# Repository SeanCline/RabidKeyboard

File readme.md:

# RabidKeyboard

This project is an ode to the old-school Cooler Master [QuickFire Rapid](https://deskthority.net/wiki/Cooler_Master_QuickFire_Rapid) TKL keyboard -- a board that introduced many people to the mechanical keyboard hobby years ago.

Over time, upgrade parts for these old mechanical keyboards have become hard to find. This project attempts to solve that by providing PCB designs that can be manufactured by services like [JLCPCB](https://jlcpcb.com/) or [PCBWay](https://www.pcbway.com/).

With the PCBs in this repository, you could:
 - Build a TKL keyboard from scratch.
 - Replace the mini-USB plug with USB-C on your Cooler Master QFR.
 - Replace the PCB in your QFR (or compatible) with a custom design running the [KMK firmware](https://github.com/KMKfw/kmk_firmware).
 - Replace the plate in your TKL keyboard with one made of FR-4 and support for more stabilizers. (Stock Costar, Cherry Plate mount, or PCB mount when the PCB is also replaced.)

## PCB
The PCB is designed in [KiCad](https://www.kicad.org/) to be easily soldered by hand. At its heart is the [RP2040 Stamp](https://www.lectronz.com/products/rp2040-stamp), which fits nicely beside the arrow keys.

## Plate
The plate is just a PCB without any copper traces. When sending it for manufacture, you can select the thickness of FR-4 to get the level of flex you like.

It's generated by copying the User.1 layer out of the PCB design and changing the layer to Edge.Cuts. The keyswitch footprints use the User.1 layer for the plate cutout which makes sure the plate cutouts always line up with the key switch location on the PCB.

> Note: This abuses the routing capabilities of a PCB manufacturer, so they'll likely charge extra for their trouble.

## Costar USB-C Daughterboard
This PCB replaces the original mini-USB daughterboard in the Cooler Master QFR. Mounting holes match the [original PCB](reference/Quickfire%20Rapid/USB%20Daughterboard%20-%20Front.jpg) so it's a drop-in replacement. A little bit of filing is required to widen the mini-USB hole the width of the USB-C port.

## YMDK USB-C Daughterboard
Just like the Cooler Master QFR, Filco Majestouch 2, and KBParadise V80, the RabidKeyboard PCB in this repo fits into the YMDK F87 aluminum case.
[[Amazon]](https://amzn.com/dp/B06XNTWXWL)
[[AliExpress]](https://www.aliexpress.us/item/2251832431251957.html)
[[Ymdkey]](https://ymdkey.com/products/f87-tkl-cnc-anodized-aluminum-case-for-filco-cm-cooler-master-87-tenkeyless)

Unfortunately, the USB daughterboard that [comes with](reference/YMDK/YMDK%20Usb%20-%20Back.png) the YMDK F87 case lacks the [required 5.1k resistors](https://hackaday.com/2023/01/04/all-about-usb-c-resistors-and-emarkers/). It works fine when plugged in using a USB-C to Type-A cable, but does not function when plugged in using a USB-C to USB-C cable. It also lacks protection circuitry. The design in this repository is a drop in replacement with some improvements:
 - 5.1k CC1 and CC2 sense resistors to work with USB-C cables.
 - [TVS diodes](https://en.wikipedia.org/wiki/Surge_protector#Transient_voltage_suppressor) to keep static shocks from reaching the microcontroller.
 - 500mA polyfuse to protect from short circuits.
 - Reverse polarity protection diode.
 - Ferrite beads to reduce high frequency EMI.

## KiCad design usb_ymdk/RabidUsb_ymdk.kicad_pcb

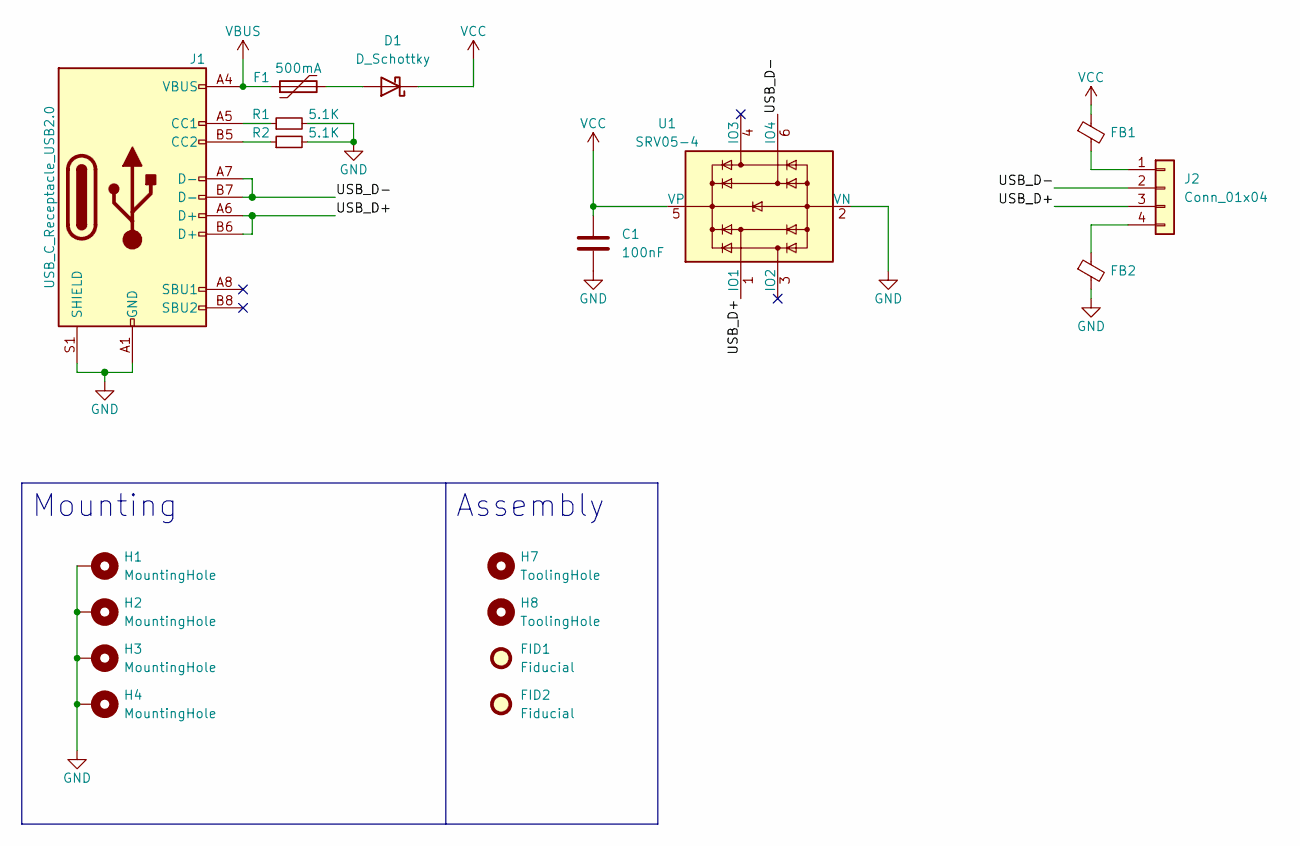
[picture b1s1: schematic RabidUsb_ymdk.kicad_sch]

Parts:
C1: 100nF; C_0603_1608Metric; LCSC C14663
D1: D_Schottky; D_SOD-123; LCSC C8598
F1: 500mA; Fuse_1812_4532Metric; LCSC C12559
FB1, FB2: FerriteBead_Small; L_0805_2012Metric; LCSC C67451
FID1, FID2: Fiducial; Fiducial_1mm_Mask2mm
H1, H2, H3, H4: MountingHole; MountingHole_.12in_Pad_.02in
H7, H8: ToolingHole; ToolingHole_1.152mm
J1: USB_C_Receptacle_USB2.0; USB_C_Receptacle_XKB_U262-16XN-4BVC11; LCSC C319148
J2: Conn_01x04; PinHeader_1x04_P2.00mm_Fingers
R1, R2: 5.1K; R_0603_1608Metric; LCSC C23186
U1: SRV05-4; SOT-23-6; LCSC C85364

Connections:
/USB_D+: J1.A6 (D+), J1.B6 (D+), J2.3, U1.1 (IO1)
/USB_D-: J1.A7 (D-), J1.B7 (D-), J2.2, U1.6 (IO4)
GND: C1.2, FB2.2, H1.1, H2.1, H3.1, H4.1, J1.A1 (GND), J1.A12 (GND), J1.B1 (GND), J1.B12 (GND), J1.S1 (SHIELD), R1.2, R2.2, U1.2 (VN)
unnamed: D1.2 (A), F1.2
unnamed: FB1.2, J2.1
unnamed: FB2.1, J2.4
unnamed: J1.A5 (CC1), R1.1
unnamed: J1.B5 (CC2), R2.1
VBUS: F1.1, J1.A4 (VBUS), J1.A9 (VBUS), J1.B4 (VBUS), J1.B9 (VBUS)
VCC: C1.1, D1.1 (K), FB1.1, U1.5 (VP)

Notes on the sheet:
Assembly
Mounting

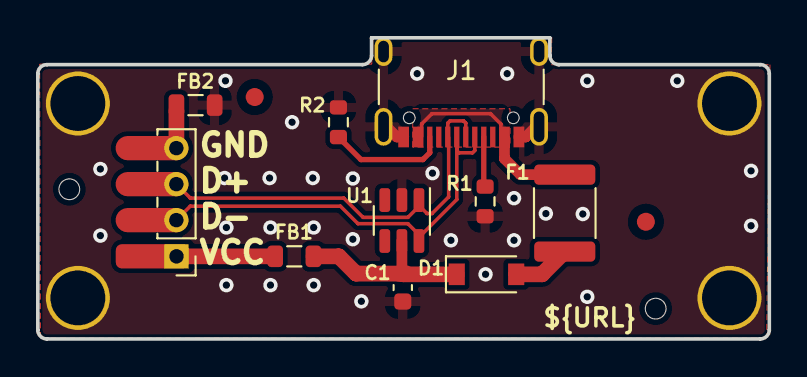
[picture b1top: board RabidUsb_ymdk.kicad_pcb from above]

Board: 2 copper layers, 40.6 x 16.7 mm, 18 parts (0 on the bottom side), 10 nets.

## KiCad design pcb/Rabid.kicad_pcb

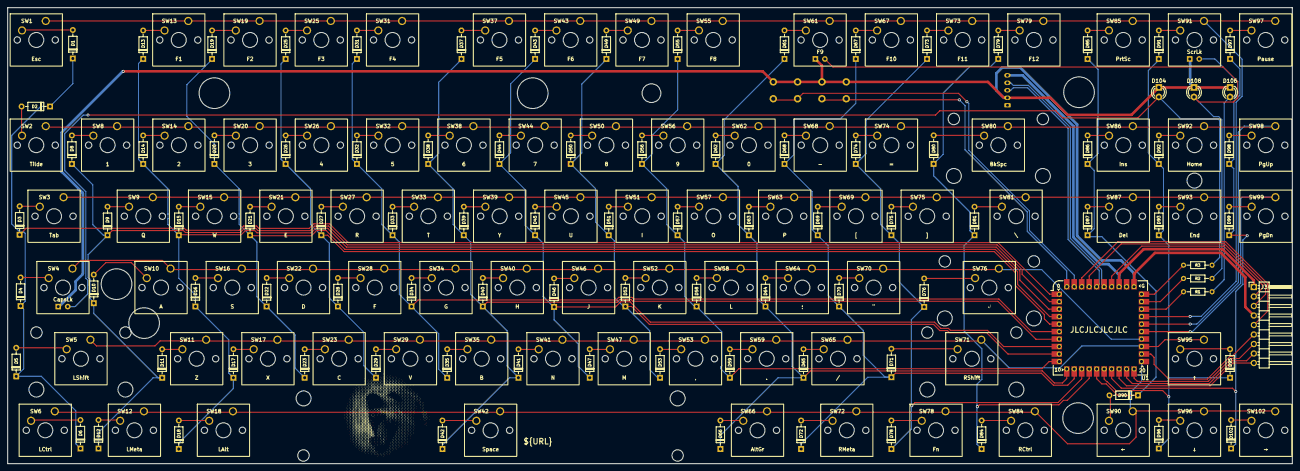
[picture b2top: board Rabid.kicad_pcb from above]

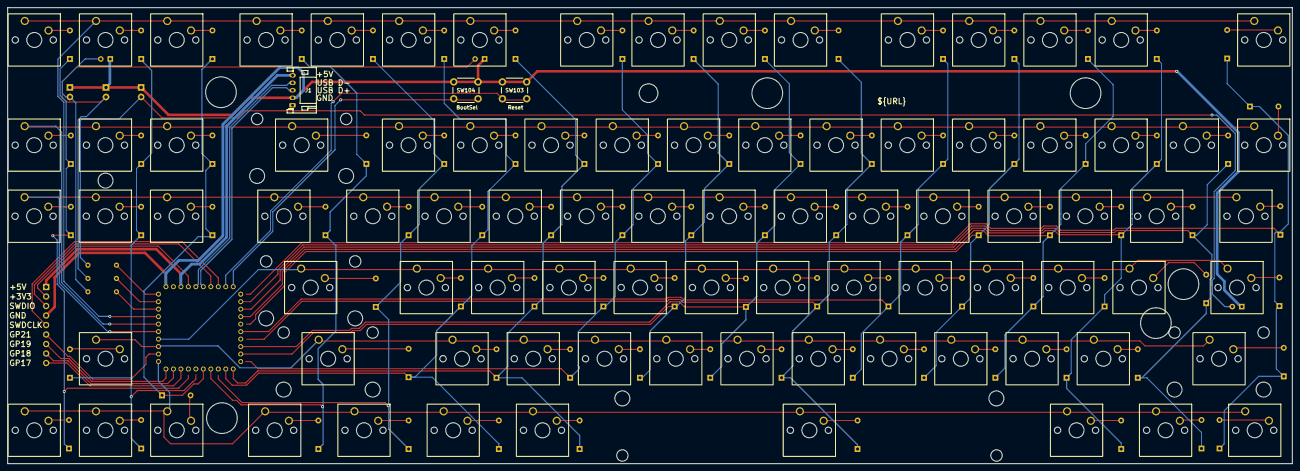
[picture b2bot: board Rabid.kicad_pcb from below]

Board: 2 copper layers, 343.4 x 121.9 mm, 194 parts (3 on the bottom side), 129 nets.

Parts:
D1, D2, D3, D4, D5, D6, D8, D9, D10, D11, D12, D13, D14, D15, D16, D17, D18, D19, D20, D21, D22, D23, D25, D26, D27, D28, D29, D31, D32, D33, D34, D35, D37, D38, D39, D40, D41, D42, D43, D44, D45, D46, D47, D49, D50, D51, D52, D53, D55, D56, D57, D58, D59, D61, D62, D63, D64, D65, D66, D67, D68, D69, D70, D71, D72, D73, D74, D75, D76, D78, D79, D80, D81, D84, D85, D86, D87, D90, D91, D92, D93, D95, D96, D97, D98, D99, D102: 1N4148; D_DO-35_SOD27_P7.62mm_Horizontal
D104: CapsLock; LED_D3.0mm
D106: ScrollLock; LED_D3.0mm
D108: MetaLock; LED_D3.0mm
G1: LOGO; RabidKeyboardLogo
H1, H2, H4, H5, H6, H7: MountingHole_8.2mm
H3: MountingHole_5mm
H8: MountingHole_4mm
J1: USB Connector; JST_PH_S5B-PH-K_1x05_P2.00mm_Horizontal
J3: GPIO Debug Header; PinHeader_1x09_P2.54mm_Horizontal
R1, R2, R3: 560; R_Axial_DIN0204_L3.6mm_D1.6mm_P7.62mm_Horizontal
SW1: Esc; SW_Cherry_MX_1.00u_PCB
SW2: Tilde; SW_Cherry_MX_1.00u_PCB
SW3: Tab; SW_Cherry_MX_1.50u_PCB
SW4: CapsLk; SW_Cherry_MX_1.75u_PCB_LED
SW5: LShift; SW_Cherry_MX_2.25u_PCB
SW6: LCtrl; SW_Cherry_MX_1.25u_PCB
SW8: 1; SW_Cherry_MX_1.00u_PCB
SW9: Q; SW_Cherry_MX_1.00u_PCB
SW10: A; SW_Cherry_MX_1.00u_PCB
SW11: Z; SW_Cherry_MX_1.00u_PCB
SW12: LMeta; SW_Cherry_MX_1.25u_PCB
SW13: F1; SW_Cherry_MX_1.00u_PCB
SW14: 2; SW_Cherry_MX_1.00u_PCB
SW15: W; SW_Cherry_MX_1.00u_PCB
SW16: S; SW_Cherry_MX_1.00u_PCB
SW17: X; SW_Cherry_MX_1.00u_PCB
SW18: LAlt; SW_Cherry_MX_1.25u_PCB
SW19: F2; SW_Cherry_MX_1.00u_PCB
SW20: 3; SW_Cherry_MX_1.00u_PCB
SW21: E; SW_Cherry_MX_1.00u_PCB
SW22: D; SW_Cherry_MX_1.00u_PCB
SW23: C; SW_Cherry_MX_1.00u_PCB
SW25: F3; SW_Cherry_MX_1.00u_PCB
SW26: 4; SW_Cherry_MX_1.00u_PCB
SW27: R; SW_Cherry_MX_1.00u_PCB
SW28: F; SW_Cherry_MX_1.00u_PCB
SW29: V; SW_Cherry_MX_1.00u_PCB
SW31: F4; SW_Cherry_MX_1.00u_PCB
SW32: 5; SW_Cherry_MX_1.00u_PCB
SW33: T; SW_Cherry_MX_1.00u_PCB
SW34: G; SW_Cherry_MX_1.00u_PCB
SW35: B; SW_Cherry_MX_1.00u_PCB
SW37: F5; SW_Cherry_MX_1.00u_PCB
SW38: 6; SW_Cherry_MX_1.00u_PCB
SW39: Y; SW_Cherry_MX_1.00u_PCB
SW40: H; SW_Cherry_MX_1.00u_PCB
SW41: N; SW_Cherry_MX_1.00u_PCB
SW42: Space; SW_Cherry_MX_6.25u_PCB_MirroredStabs
SW43: F6; SW_Cherry_MX_1.00u_PCB
SW44: 7; SW_Cherry_MX_1.00u_PCB
SW45: U; SW_Cherry_MX_1.00u_PCB
SW46: J; SW_Cherry_MX_1.00u_PCB
SW47: M; SW_Cherry_MX_1.00u_PCB
SW49: F7; SW_Cherry_MX_1.00u_PCB
SW50: 8; SW_Cherry_MX_1.00u_PCB
SW51: I; SW_Cherry_MX_1.00u_PCB
SW52: K; SW_Cherry_MX_1.00u_PCB
SW53: ,; SW_Cherry_MX_1.00u_PCB
SW55: F8; SW_Cherry_MX_1.00u_PCB
SW56: 9; SW_Cherry_MX_1.00u_PCB
SW57: O; SW_Cherry_MX_1.00u_PCB
SW58: L; SW_Cherry_MX_1.00u_PCB
SW59: .; SW_Cherry_MX_1.00u_PCB
SW61: F9; SW_Cherry_MX_1.00u_PCB_LED
SW62: 0; SW_Cherry_MX_1.00u_PCB
SW63: P; SW_Cherry_MX_1.00u_PCB
SW64: ;; SW_Cherry_MX_1.00u_PCB
SW65: /; SW_Cherry_MX_1.00u_PCB
SW66: AltGr; SW_Cherry_MX_1.25u_PCB
SW67: F10; SW_Cherry_MX_1.00u_PCB
SW68: -; SW_Cherry_MX_1.00u_PCB
SW69: [; SW_Cherry_MX_1.00u_PCB
SW70: "; SW_Cherry_MX_1.00u_PCB
SW71: RShift; SW_Cherry_MX_2.75u_PCB
SW72: RMeta; SW_Cherry_MX_1.25u_PCB
SW73: F11; SW_Cherry_MX_1.00u_PCB
SW74: =; SW_Cherry_MX_1.00u_PCB
SW75: ]; SW_Cherry_MX_1.00u_PCB
SW76: ↲; SW_Cherry_MX_2.25u_PCB
SW78: Fn; SW_Cherry_MX_1.25u_PCB
SW79: F12; SW_Cherry_MX_1.00u_PCB
SW80: BkSpc; SW_Cherry_MX_2.00u_PCB
SW81: \; SW_Cherry_MX_1.50u_PCB
SW84: RCtrl; SW_Cherry_MX_1.25u_PCB
SW85: PrtSc; SW_Cherry_MX_1.00u_PCB
SW86: Ins; SW_Cherry_MX_1.00u_PCB
SW87: Del; SW_Cherry_MX_1.00u_PCB
SW90: ←; SW_Cherry_MX_1.00u_PCB
SW91: ScrLk; SW_Cherry_MX_1.00u_PCB_LED
SW92: Home; SW_Cherry_MX_1.00u_PCB
SW93: End; SW_Cherry_MX_1.00u_PCB
SW95: ↑; SW_Cherry_MX_1.00u_PCB
SW96: ↓; SW_Cherry_MX_1.00u_PCB
SW97: Pause; SW_Cherry_MX_1.00u_PCB
SW98: PgUp; SW_Cherry_MX_1.00u_PCB
SW99: PgDn; SW_Cherry_MX_1.00u_PCB
SW102: →; SW_Cherry_MX_1.00u_PCB
SW103: Reset; SW_PUSH_6mm
SW104: BootSel; SW_PUSH_6mm
U1: RP2040_Stamp; RP2040_Stamp_THT

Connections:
+3V3: J3.2, U1.34 (3.3V)
+5V: J1.5, J3.1, U1.33 (5V)
/BOOTSEL: SW104.2, U1.40 (BOOTSEL)
/CapsLED: D104.2 (A), R3.2, SW4.4 (A)
/CapsLED_GPIO: R3.1, U1.30 (GPIO29)
/GPIO17: J3.9, U1.18 (GPIO17)
/GPIO18: J3.8, U1.19 (GPIO18)
/GPIO19: J3.7, U1.20 (GPIO19)
/GPIO21: J3.6, U1.22 (GPIO21)
/MetaLED: D108.2 (A), R2.2, SW61.4 (A)
/MetaLED_GPIO: R2.1, U1.29 (GPIO28)
/SWCLK: J3.5, U1.38 (SWCLK)
/SWDIO: J3.3, U1.37 (SWDIO)
/ScrollLED: D106.2 (A), R1.2, SW91.4 (A)
/ScrollLED_GPIO: R1.1, U1.28 (GPIO27)
/USB_D+: J1.3, U1.36 (USB_D+)
/USB_D-: J1.4, U1.35 (USB_D-)
/~RESET: SW103.2, U1.39 (~RESET)
ColA: D1.1 (K), D2.1 (K), D3.1 (K), D4.1 (K), D5.1 (K), D6.1 (K), U1.1 (GPIO0)
ColB: D8.1 (K), D9.1 (K), D10.1 (K), D11.1 (K), D12.1 (K), U1.2 (GPIO1)
ColC: D13.1 (K), D14.1 (K), D15.1 (K), D16.1 (K), D17.1 (K), D18.1 (K), U1.3 (GPIO2)
ColD: D19.1 (K), D20.1 (K), D21.1 (K), D22.1 (K), D23.1 (K), U1.4 (GPIO3)
ColE: D25.1 (K), D26.1 (K), D27.1 (K), D28.1 (K), D29.1 (K), U1.5 (GPIO4)
ColF: D31.1 (K), D32.1 (K), D33.1 (K), D34.1 (K), D35.1 (K), U1.6 (GPIO5)
ColG: D37.1 (K), D38.1 (K), D39.1 (K), D40.1 (K), D41.1 (K), D42.1 (K), U1.7 (GPIO6)
ColH: D43.1 (K), D44.1 (K), D45.1 (K), D46.1 (K), D47.1 (K), U1.8 (GPIO7)
ColI: D49.1 (K), D50.1 (K), D51.1 (K), D52.1 (K), D53.1 (K), U1.9 (GPIO8)
ColJ: D55.1 (K), D56.1 (K), D57.1 (K), D58.1 (K), D59.1 (K), U1.10 (GPIO9)
ColK: D61.1 (K), D62.1 (K), D63.1 (K), D64.1 (K), D65.1 (K), D66.1 (K), U1.11 (GPIO10)
ColL: D67.1 (K), D68.1 (K), D69.1 (K), D70.1 (K), D71.1 (K), D72.1 (K), U1.12 (GPIO11)
ColM: D73.1 (K), D74.1 (K), D75.1 (K), D76.1 (K), D78.1 (K), U1.13 (GPIO12)
ColN: D79.1 (K), D80.1 (K), D81.1 (K), D84.1 (K), U1.14 (GPIO13)
ColO: D85.1 (K), D86.1 (K), D87.1 (K), D90.1 (K), U1.15 (GPIO14)
ColP: D91.1 (K), D92.1 (K), D93.1 (K), D95.1 (K), D96.1 (K), U1.16 (GPIO15)
ColQ: D97.1 (K), D98.1 (K), D99.1 (K), D102.1 (K), U1.17 (GPIO16)
GND: D104.1 (K), D106.1 (K), D108.1 (K), J1.2, J3.4, SW4.3 (K), SW61.3 (K), SW91.3 (K), SW103.1, SW104.1, U1.31 (GND)
unnamed: D1.2 (A), SW1.2
unnamed: D2.2 (A), SW2.2
unnamed: D3.2 (A), SW3.2
unnamed: D4.2 (A), SW4.2
unnamed: D5.2 (A), SW5.2
unnamed: D6.2 (A), SW6.2
unnamed: D8.2 (A), SW8.2
unnamed: D9.2 (A), SW9.2
unnamed: D10.2 (A), SW10.2
unnamed: D11.2 (A), SW11.2
unnamed: D12.2 (A), SW12.2
unnamed: D13.2 (A), SW13.2
unnamed: D14.2 (A), SW14.2
unnamed: D15.2 (A), SW15.2
unnamed: D16.2 (A), SW16.2
unnamed: D17.2 (A), SW17.2
unnamed: D18.2 (A), SW18.2
unnamed: D19.2 (A), SW19.2
unnamed: D20.2 (A), SW20.2
unnamed: D21.2 (A), SW21.2
unnamed: D22.2 (A), SW22.2
unnamed: D23.2 (A), SW23.2
unnamed: D25.2 (A), SW25.2
unnamed: D26.2 (A), SW26.2
unnamed: D27.2 (A), SW27.2
unnamed: D28.2 (A), SW28.2
unnamed: D29.2 (A), SW29.2
unnamed: D31.2 (A), SW31.2
unnamed: D32.2 (A), SW32.2
unnamed: D33.2 (A), SW33.2
unnamed: D34.2 (A), SW34.2
unnamed: D35.2 (A), SW35.2
unnamed: D37.2 (A), SW37.2
unnamed: D38.2 (A), SW38.2
unnamed: D39.2 (A), SW39.2
unnamed: D40.2 (A), SW40.2
unnamed: D41.2 (A), SW41.2
unnamed: D42.2 (A), SW42.2
unnamed: D43.2 (A), SW43.2
unnamed: D44.2 (A), SW44.2
unnamed: D45.2 (A), SW45.2
unnamed: D46.2 (A), SW46.2
unnamed: D47.2 (A), SW47.2
unnamed: D49.2 (A), SW49.2
unnamed: D50.2 (A), SW50.2
unnamed: D51.2 (A), SW51.2
unnamed: D52.2 (A), SW52.2
unnamed: D53.2 (A), SW53.2
unnamed: D55.2 (A), SW55.2
unnamed: D56.2 (A), SW56.2
unnamed: D57.2 (A), SW57.2
unnamed: D58.2 (A), SW58.2
unnamed: D59.2 (A), SW59.2
unnamed: D61.2 (A), SW61.2
unnamed: D62.2 (A), SW62.2
unnamed: D63.2 (A), SW63.2
unnamed: D64.2 (A), SW64.2
unnamed: D65.2 (A), SW65.2
unnamed: D66.2 (A), SW66.2
unnamed: D67.2 (A), SW67.2
unnamed: D68.2 (A), SW68.2
unnamed: D69.2 (A), SW69.2
unnamed: D70.2 (A), SW70.2
unnamed: D71.2 (A), SW71.2
unnamed: D72.2 (A), SW72.2
unnamed: D73.2 (A), SW73.2
unnamed: D74.2 (A), SW74.2
unnamed: D75.2 (A), SW75.2
unnamed: D76.2 (A), SW76.2
unnamed: D78.2 (A), SW78.2
unnamed: D79.2 (A), SW79.2
unnamed: D80.2 (A), SW80.2
unnamed: D81.2 (A), SW81.2
unnamed: D84.2 (A), SW84.2
unnamed: D85.2 (A), SW85.2
unnamed: D86.2 (A), SW86.2
unnamed: D87.2 (A), SW87.2
unnamed: D90.2 (A), SW90.2
unnamed: D91.2 (A), SW91.2
unnamed: D92.2 (A), SW92.2
unnamed: D93.2 (A), SW93.2
unnamed: D95.2 (A), SW95.2
unnamed: D96.2 (A), SW96.2
unnamed: D97.2 (A), SW97.2
unnamed: D98.2 (A), SW98.2
unnamed: D99.2 (A), SW99.2
unnamed: D102.2 (A), SW102.2
Row0: SW1.1, SW13.1, SW19.1, SW25.1, SW31.1, SW37.1, SW43.1, SW49.1, SW55.1, SW61.1, SW67.1, SW73.1, SW79.1, SW85.1, SW91.1, SW97.1, U1.27 (GPIO26)
Row1: SW2.1, SW8.1, SW14.1, SW20.1, SW26.1, SW32.1, SW38.1, SW44.1, SW50.1, SW56.1, SW62.1, SW68.1, SW74.1, SW80.1, SW86.1, SW92.1, SW98.1, U1.26 (GPIO25)
Row2: SW3.1, SW9.1, SW15.1, SW21.1, SW27.1, SW33.1, SW39.1, SW45.1, SW51.1, SW57.1, SW63.1, SW69.1, SW75.1, SW81.1, SW87.1, SW93.1, SW99.1, U1.25 (GPIO24)
Row3: SW4.1, SW10.1, SW16.1, SW22.1, SW28.1, SW34.1, SW40.1, SW46.1, SW52.1, SW58.1, SW64.1, SW70.1, SW76.1, U1.24 (GPIO23)
Row4: SW5.1, SW11.1, SW17.1, SW23.1, SW29.1, SW35.1, SW41.1, SW47.1, SW53.1, SW59.1, SW65.1, SW71.1, SW95.1, U1.23 (GPIO22)
Row5: SW6.1, SW12.1, SW18.1, SW42.1, SW66.1, SW72.1, SW78.1, SW84.1, SW90.1, SW96.1, SW102.1, U1.21 (GPIO20)

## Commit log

2022-05-26 Initial Commit.
    Schematic mostly done.
    PCB components arranged logically but needs laid out.
2022-05-27 Everything in its approximate location.
    TODO:
    - Still needs comparison to a real PCB to get measurements more accurate.
    - Needs mounting holes.
2022-05-27 Name the keys on F.Fab layer.
2022-05-27 Made measurements more precise.
2022-05-28 Add mounting holes.
2022-05-28 LED tracks routed.
2022-05-28 Tidy up the USB connector nets.
2022-05-29 Routed arrows keys and rows.
2022-05-29 Route columns. Board is now fully routed.
2022-05-29 Adjusted location of keys to match plate mount holes.
2022-05-29 Remove unused footprint library.
2022-05-29 Flip stabilizers on spacebar to fit on the board.
    Spacebar footprint is now broken out into its own library.
2022-05-29 Fixed several DRC errors.
    - Moved silkscreens into component footprints to keep them from overlapping.
    - Re-routed USB traces as a differential pair.
2022-05-29 Create a separate footprint for MX switches with LED.
2022-05-30 Changed dimensions, moved function row up, added mounting hole.
2022-05-30 Add GPIO/Debug header, bootsel, and reset switch.
2022-05-30 Add silkscreen labels and tidy microcontroller traces.
2022-05-30 Add project title/author/revision/url to silkscreen.
2022-05-31 Flip USB pinout to match original PCB.
2022-05-31 Change all mounting holes to 8.2mm diameter.
2022-05-31 Change DRC rules to match JLCPCB.
    - Fixed some DRC errors by adjusting tolerances.
    (Seems Kicad has some rounding error in differential pair gap DRC?)
    - Add "JLCJLCJLCJLC" to silkscreen for JLCPCB to replace with order number.
    - Slight adjustments to mounting holes.
2022-05-31 Add switch outline on back silkscreen for easier assembly.
2022-06-02 Make Filco mounting hole smaller.
    - Add logo under spacebar.
    - Change PCB colour to black.
2022-06-02 Change RP2040 Stamp footprint to throughhole.
    This ismore versatile as it allows either SMD or soldering on 2mm
    pinheaders to use as a socket.
2022-06-02 Make the power traces .7mm because I'm paranoid.
2022-06-03 Swap GPIO20 and GPIO21 (ROW0) pins.
    The RP2040 Stamp has a WS2812B LED on the GPIO21 line.
    It does have a jumper to disable the LED, but better to just work
    around it, so it remains usable.
2022-06-03 Change Filco hole from 4mm to 5mm.
    - Rename FnLock to MetaLock.
    - Minor silkscreen changes.
2022-06-03 Generate Gerbers and send to JLPCB.
2022-06-09 Add plate cutouts to the User.1 layer.
    The intention is that this layer can be plotted as a Gerber and renamed
    to be the EdgeCuts. That way, the plate cutouts _always_ match the
    switch locations on the PCB.
    Cutout dimensions are heavily inspired by (read: stolen from) the
    awesome: http://builder.swillkb.com/
    Switch cutouts are square for maximum stability. Stabilizers are
2022-06-09 Add margin around the plate, LED and mount holes.
2022-06-10 Tweak plate size to match QFR case.
2022-06-12 Add holes in plate to press BootSel/Reset button.
    If the BootSel and Reset buttons don't fit in the case when installed on
    the back of the board, then they have a chance of fitting between the
    plate and PCB. A hole in the plate will let them be pressed with a small
    screwdriver.
2022-06-21 FW: Preliminary (untested) firmware based on KMK.
    https://github.com/KMKfw/kmk_firmware
2022-06-21 Reverse direction of row pins to match firmware.
2022-06-21 Add reference photos for QFR plate and controller.
2022-06-21 FW: Fix the column pins.
2022-06-28 Generate plate from the PCB Plate.Cutouts (User.1) layer.
2022-06-28 Reorganize directory structure.
    Put the PCB in its own folder to keep it separate from plate and firmware.
2022-06-28 Tidy up the gerber outputs.
    pcb/gerbers and plate/gerbers now contain the 1.0 version sent to JLCPCB
    for manufacture, along with the "production file"created by JLC.
2022-07-17 PCB: Move D5 and D80 over just a bit so they don't interfere with stabilizers
2022-07-17 PCB: Swap Reset and BootSel button silkscreens.
2022-07-27 USB: Add QFR USB board reference photos.
2022-07-27 USB: Initial commit of QFR (costar) USB-C daughterboard.
2022-07-27 USB: Update tooling holes to match what JLCPCB needed for assembly.
2022-07-29 USB: Add reference photos for YMDK USB daughterboard.
2022-08-07 USB: Initial commit of YMDK USB-C daughterboard.
2022-08-07 Tidy up JLCPCB production files.
2022-08-08 USB: More ground plane between VCC and D+/D-.
2022-08-24 USB: Add ferrite beads to YMDK USB board.
2022-09-12 USB: Add production files for usb_ymdk board.
2022-09-14 USB: Add 3D models for USB connector and fuse.
2022-09-14 USB: Add ferrite beads to usb_costar board as well.
2022-09-14 Add images/renders of all boards and schematics.
2022-09-14 FW: Blink the Fn light during boot for feedback.
2022-09-14 FW: Speed up the matrix polling rate.
2022-09-14 USB: Move usb_ymdk holes up a couple thou.
    This should helpfully give some more room, so the board isn't such a
    tight fit in the YMDK F87 case.
2023-01-17 FW: Add more robust error handling.
    1) On startup, the board now waits for USB to be connected. This works
    around a quirk in CircuitPython where accessing USB before it's ready
    causes Windows to give up with the error:: "Unknown USB device (device
    descriptor request failed)".
    2) When an exception unwinds all the way to main(), the error message is
    written to flash and a reset is attempted after a delay. This reset
2023-01-17 FW: Support CircuitPython 8.0beta6.
    The `next_stack_limit` had a minor API change.
    This supports both 7.0 and 8.0 for now.
2023-01-30 Docs: Add a first draft of readme.
2023-01-31 Add a license and fix some typos.
2023-02-03 PCB: Add a ground pour to both sides of the board.
    There's a via near each key. Hopefully this fixes issue #1.
2024-07-13 Fix a typo.
2024-09-26 Add macro recording.
    Select macro slot: Fn+Number
    Record: Fn+`
    Stop recording: Fn+Backspace
    Play: Fn+Return
2024-09-26 Remove stack limit from boot.py.
    This doesn't seem to be required with recent versions of KMK and
    CircuitPython >=9.0.
2025-04-07 FW: Add a MouseJiggler feature toggled by Fn+ScrollLock.
2025-04-07 FW: Fix to run against latest KMK.
2025-04-07 FW: Turn on debouncing and speed up scan interval.
2025-04-10 FW: Pulse the scroll lock LED when the mouse jiggler is on.
2025-04-10 FW: Use KMK's new boot_cfg module instead of custom boot.py logic
2025-04-10 FW: Remove error logging now that KMK catches exceptions.
    https://github.com/KMKfw/kmk_firmware/commit/e79414e0582b81de98c9a0fce57988da292a0f39
2025-04-10 FW: Throttle LED status updates and fix a float precision bug.
2025-04-22 FW: Use the mouse jiggler module that ships with KMK.
    The mouse jiggler module is now upstreamed into KMK.
    https://github.com/KMKfw/kmk_firmware/pull/1103
    We can just import the upstreamed version instead of our own copy.
2026-05-16 FW: Minor updates.
    - Make self.matrix a list to avoid a fallback codepath in KMK.
    - Keep the Fn-lock LED lit when the layer is selected an Fn is pressed.
    -Import `Pin` since we use type annotations.
